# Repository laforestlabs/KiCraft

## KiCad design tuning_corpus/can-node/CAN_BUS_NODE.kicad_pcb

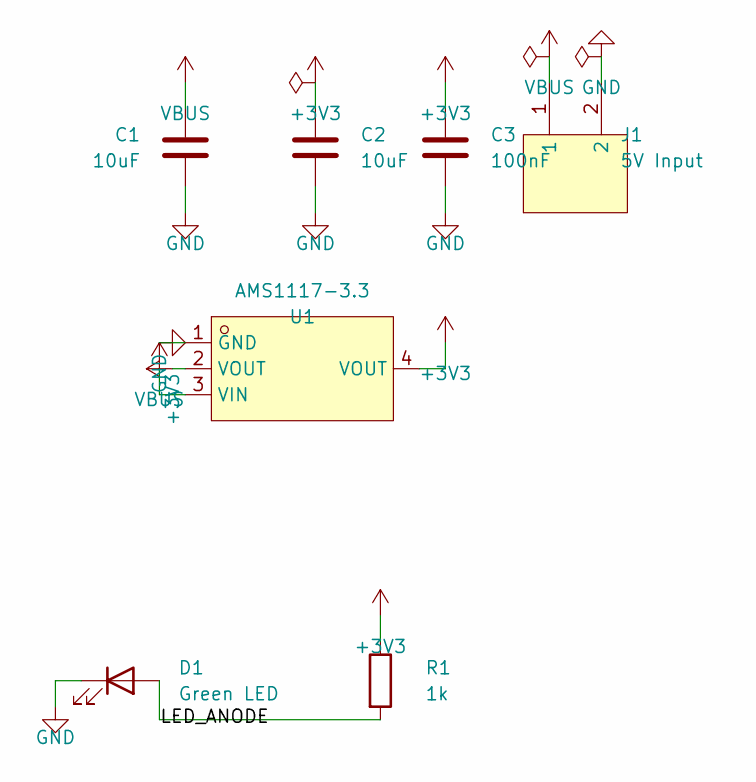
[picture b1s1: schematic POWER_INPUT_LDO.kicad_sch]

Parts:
C1, C2: 10uF; C_0805_2012Metric
C3: 100nF; C_0805_2012Metric
D1: Green LED; LED_0805_2012Metric
J1: 5V Input; CONN-TH_WJ126V-5.0-2P
R1: 1k; R_0805_2012Metric
U1: AMS1117-3.3; SOT-223-3_L6.5-W3.4-P2.30-LS7.0-BR

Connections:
LED_ANODE: D1.2 (A), R1.2

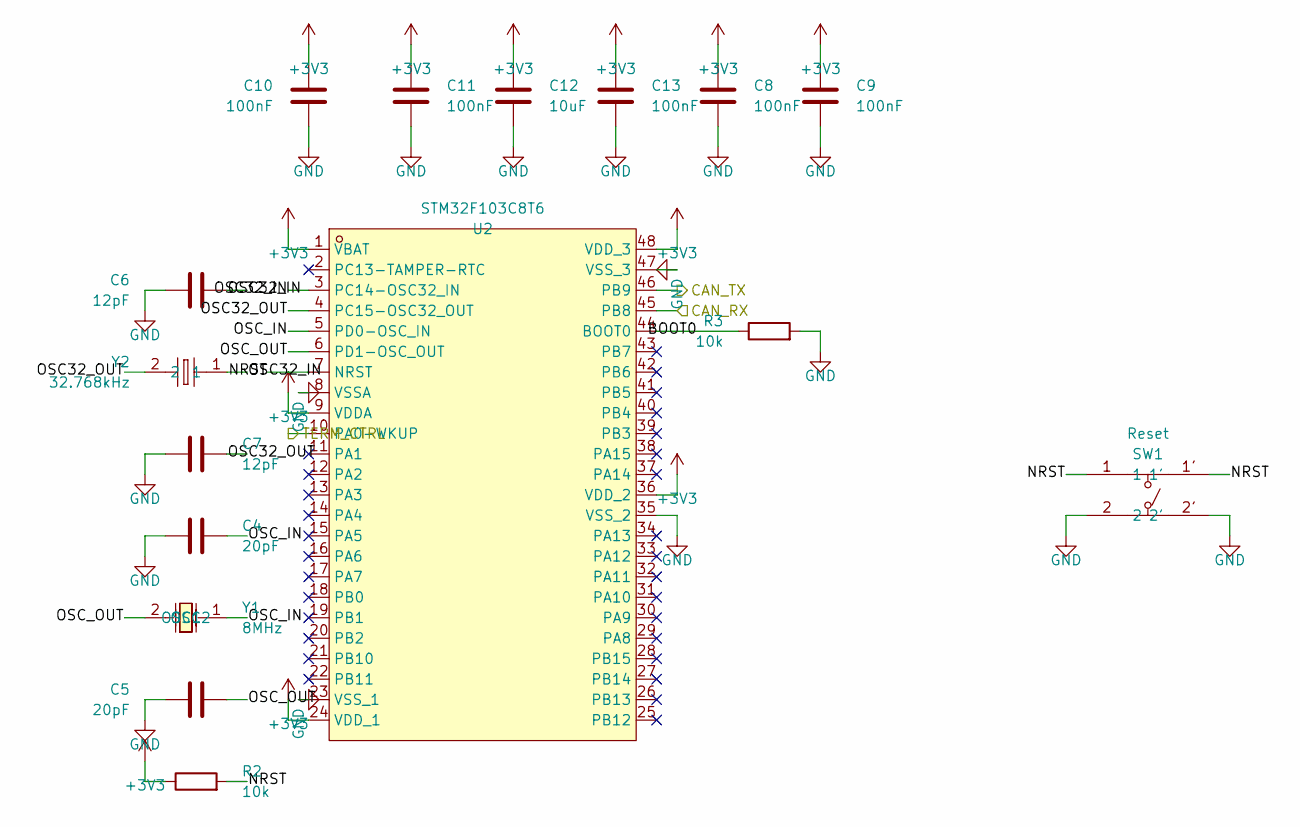
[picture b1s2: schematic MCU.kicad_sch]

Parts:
C4, C5: 20pF; C_0805_2012Metric
C6, C7: 12pF; C_0805_2012Metric
C8, C9, C10, C11, C13: 100nF; C_0805_2012Metric
C12: 10uF; C_0805_2012Metric
R2, R3: 10k; R_0805_2012Metric
SW1: Reset; SW-SMD_EVQP7A01P
U2: STM32F103C8T6; LQFP-48_L7.0-W7.0-P0.50-LS9.0-BL
Y1: 8MHz; CRYSTAL-SMD_L11.5-W4.8-LS12.7
Y2: 32.768kHz; OSC-SMD_L3.2-W1.5

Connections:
BOOT0: R3.1, U2.44 (BOOT0)
CAN_RX: U2.45 (PB8); also elsewhere on the board
CAN_TX: U2.46 (PB9); also elsewhere on the board
NRST: R2.2, SW1.1, SW1.1', U2.7 (NRST)
OSC32_IN: C6.1, U2.3 (PC14-OSC32_IN), Y2.1
OSC32_OUT: C7.1, U2.4 (PC15-OSC32_OUT), Y2.2
OSC_IN: C4.1, U2.5 (PD0-OSC_IN), Y1.1 (OSC1)
OSC_OUT: C5.1, U2.6 (PD1-OSC_OUT), Y1.2 (OSC2)
TERM_CTRL: U2.10 (PA0-WKUP); also elsewhere on the board

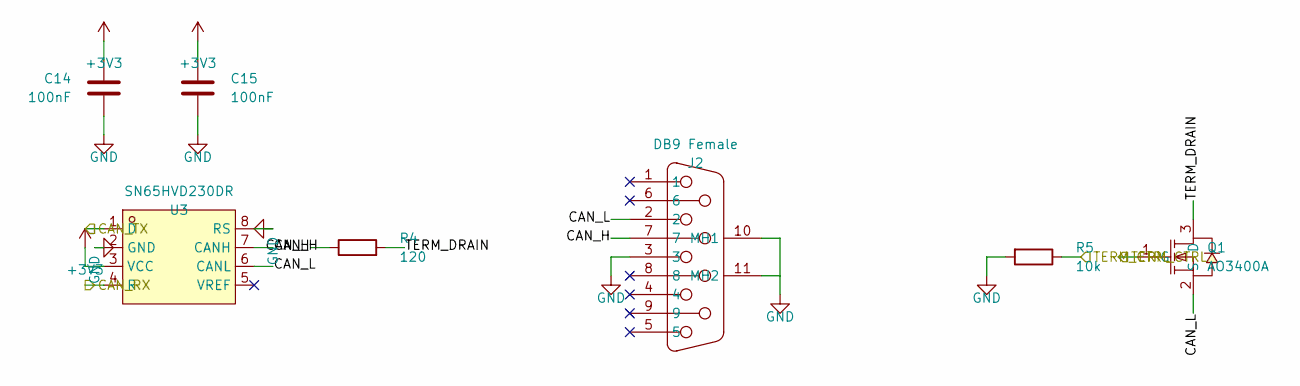
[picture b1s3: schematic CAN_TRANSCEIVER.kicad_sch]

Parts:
C14, C15: 100nF; C_0805_2012Metric
J2: DB9 Female; DSUB-TH_DMR-9S
Q1: AO3400A; SOT-23-3_L2.9-W1.3-P1.90-LS2.4-BR
R4: 120; R_0805_2012Metric
R5: 10k; R_0805_2012Metric
U3: SN65HVD230DR; SOIC-8_L4.9-W3.9-P1.27-LS6.0-BL

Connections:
CAN_H: J2.7, R4.1, U3.7 (CANH)
CAN_L: J2.2, Q1.2 (S), U3.6 (CANL)
CAN_RX: U3.4 (R); also elsewhere on the board
CAN_TX: U3.1 (D); also elsewhere on the board
TERM_CTRL: Q1.1 (G), R5.1; also elsewhere on the board
TERM_DRAIN: Q1.3 (D), R4.2

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
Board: 2 copper layers, 30 parts (0 on the bottom side), 16 nets, no tracks yet.

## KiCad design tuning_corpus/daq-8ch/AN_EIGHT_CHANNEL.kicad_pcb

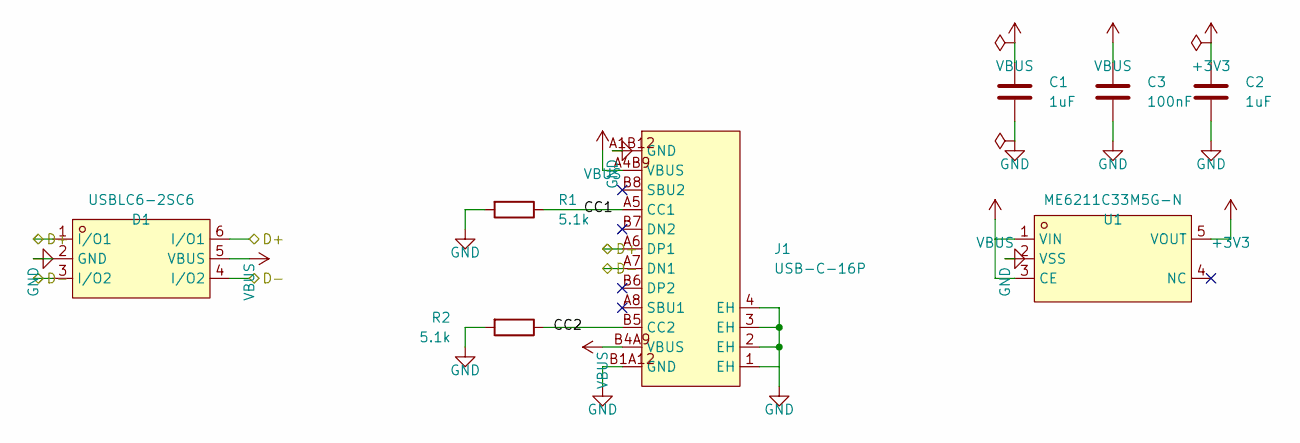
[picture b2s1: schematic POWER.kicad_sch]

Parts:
C1, C2: 1uF; C_0805_2012Metric
C3: 100nF; C_0805_2012Metric
D1: USBLC6-2SC6; SOT-23-6_L2.9-W1.6-P0.95-LS2.8-BL
J1: USB-C-16P; USB-C_SMD-TYPE-C-31-M-12_1
R1, R2: 5.1k; R_0805_2012Metric
U1: ME6211C33M5G-N; SOT-23-5_L3.0-W1.7-P0.95-LS2.8-BL

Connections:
CC1: J1.A5 (CC1), R1.1
CC2: J1.B5 (CC2), R2.1
D+: D1.1 (I/O1), D1.6 (I/O1), J1.A6 (DP1); also elsewhere on the board
D-: D1.3 (I/O2), D1.4 (I/O2), J1.A7 (DN1); also elsewhere on the board

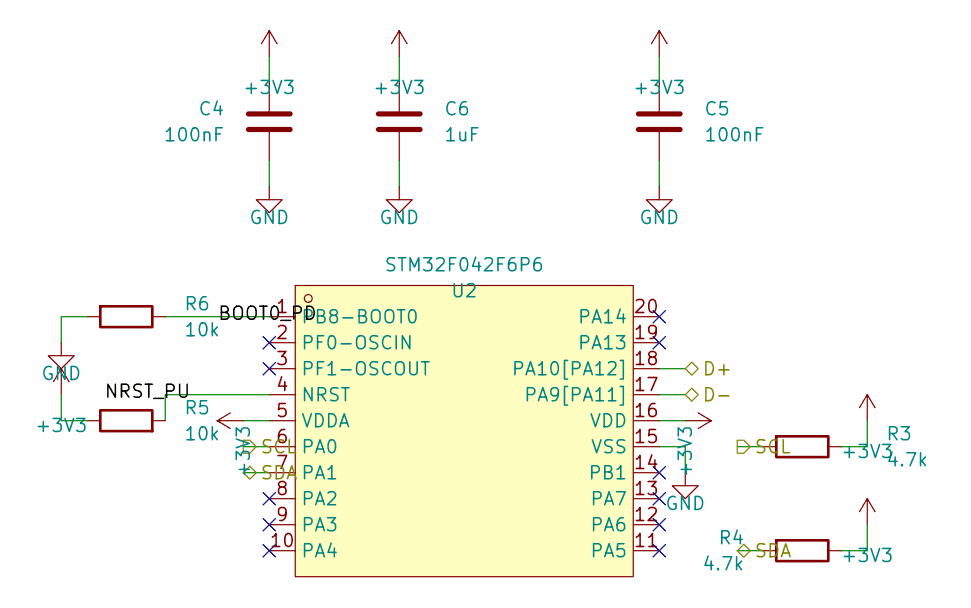
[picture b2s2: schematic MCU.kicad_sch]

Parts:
C4, C5: 100nF; C_0805_2012Metric
C6: 1uF; C_0805_2012Metric
R3, R4: 4.7k; R_0805_2012Metric
R5, R6: 10k; R_0805_2012Metric
U2: STM32F042F6P6; TSSOP-20_L6.5-W4.4-P0.65-LS6.4-BL

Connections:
BOOT0_PD: R6.1, U2.1 (PB8-BOOT0)
D+: U2.18 (PA10[PA12]); also elsewhere on the board
D-: U2.17 (PA9[PA11]); also elsewhere on the board
NRST_PU: R5.2, U2.4 (NRST)
SCL: R3.2, U2.6 (PA0); also elsewhere on the board
SDA: R4.2, U2.7 (PA1); also elsewhere on the board

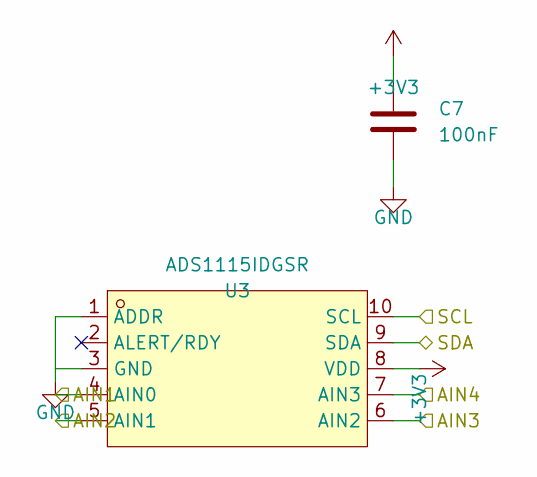
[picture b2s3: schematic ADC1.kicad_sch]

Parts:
C7: 100nF; C_0805_2012Metric
U3: ADS1115IDGSR; MSOP-10_L3.0-W3.0-P0.50-LS5.0-BL

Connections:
AIN1: U3.4 (AIN0); also elsewhere on the board
AIN2: U3.5 (AIN1); also elsewhere on the board
AIN3: U3.6 (AIN2); also elsewhere on the board
AIN4: U3.7 (AIN3); also elsewhere on the board
SCL: U3.10 (SCL); also elsewhere on the board
SDA: U3.9 (SDA); also elsewhere on the board

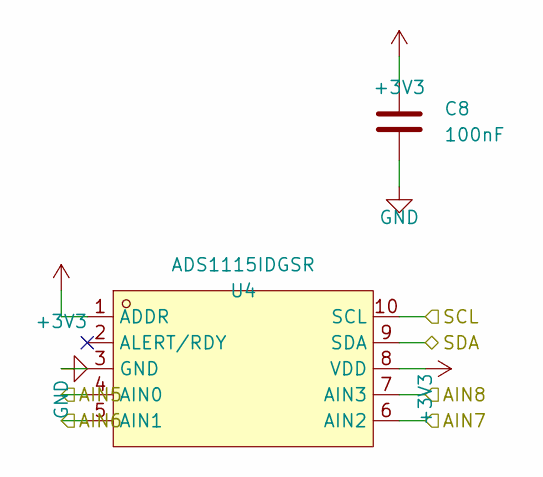
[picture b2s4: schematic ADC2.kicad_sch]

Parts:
C8: 100nF; C_0805_2012Metric
U4: ADS1115IDGSR; MSOP-10_L3.0-W3.0-P0.50-LS5.0-BL

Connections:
AIN5: U4.4 (AIN0); also elsewhere on the board
AIN6: U4.5 (AIN1); also elsewhere on the board
AIN7: U4.6 (AIN2); also elsewhere on the board
AIN8: U4.7 (AIN3); also elsewhere on the board
SCL: U4.10 (SCL); also elsewhere on the board
SDA: U4.9 (SDA); also elsewhere on the board

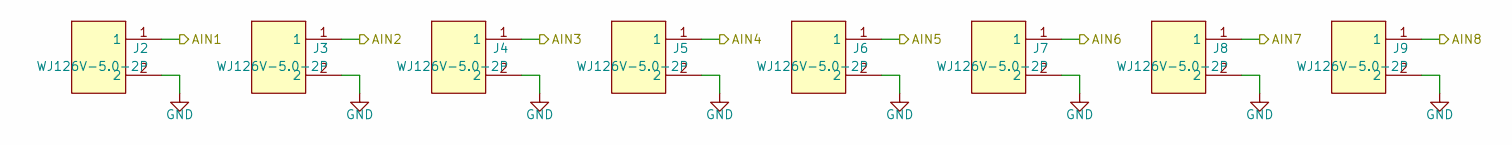
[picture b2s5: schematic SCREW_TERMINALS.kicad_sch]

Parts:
J2, J3, J4, J5, J6, J7, J8, J9: WJ126V-5.0-2P; CONN-TH_WJ126V-5.0-2P

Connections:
AIN1: J2.1; also elsewhere on the board
AIN2: J3.1; also elsewhere on the board
AIN3: J4.1; also elsewhere on the board
AIN4: J5.1; also elsewhere on the board
AIN5: J6.1; also elsewhere on the board
AIN6: J7.1; also elsewhere on the board
AIN7: J8.1; also elsewhere on the board
AIN8: J9.1; also elsewhere on the board

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
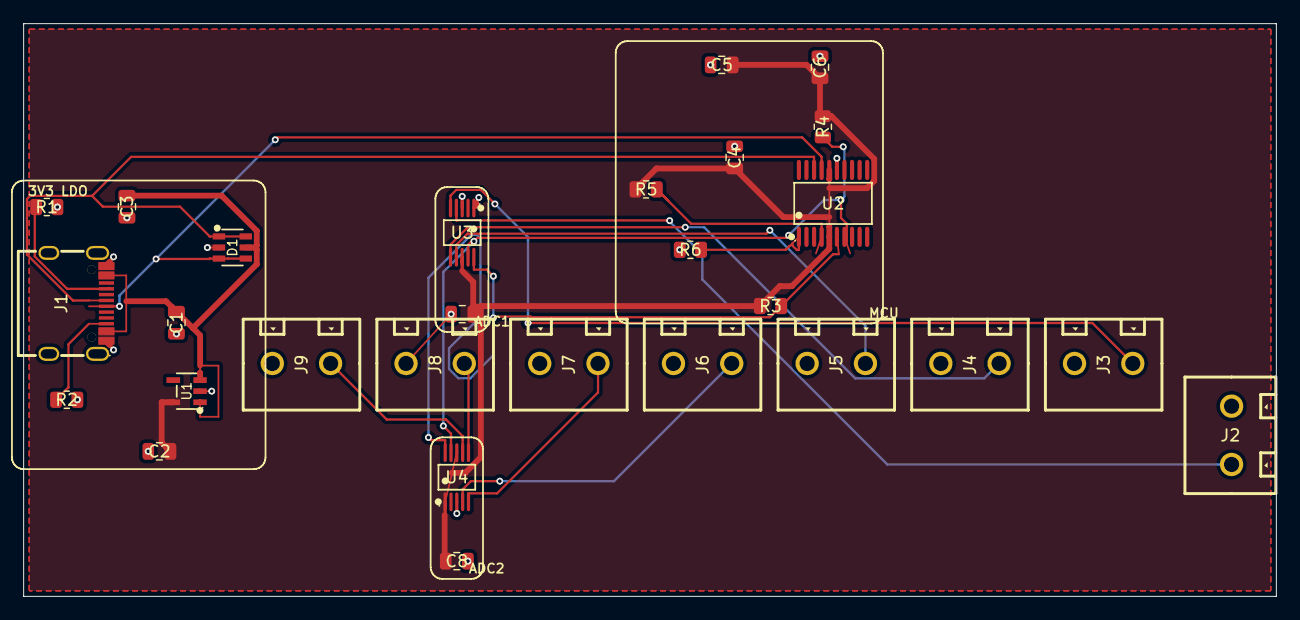
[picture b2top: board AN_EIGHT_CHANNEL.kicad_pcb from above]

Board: 2 copper layers, 107.5 x 49.1 mm, 28 parts (0 on the bottom side), 19 nets.

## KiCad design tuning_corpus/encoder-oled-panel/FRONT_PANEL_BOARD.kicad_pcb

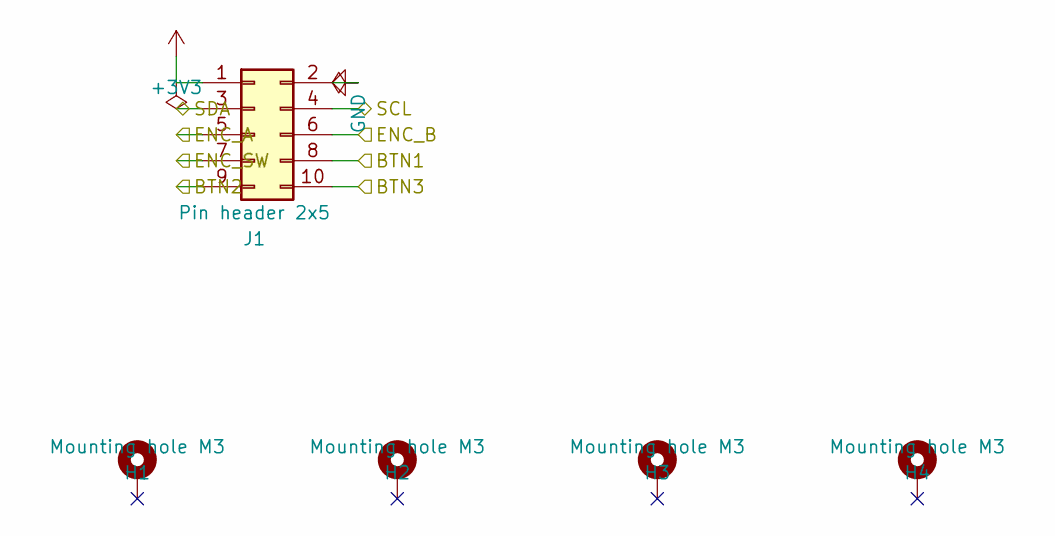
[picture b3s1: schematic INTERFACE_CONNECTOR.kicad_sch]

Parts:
H1, H2, H3, H4: Mounting hole M3; MountingHole_3.2mm_M3_Pad_TopBottom
J1: Pin header 2x5; PinHeader_2x05_P2.54mm_Vertical

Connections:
BTN1: J1.8; also elsewhere on the board
BTN2: J1.9; also elsewhere on the board
BTN3: J1.10; also elsewhere on the board
ENC_A: J1.5; also elsewhere on the board
ENC_B: J1.6; also elsewhere on the board
ENC_SW: J1.7; also elsewhere on the board
SCL: J1.4; also elsewhere on the board
SDA: J1.3; also elsewhere on the board

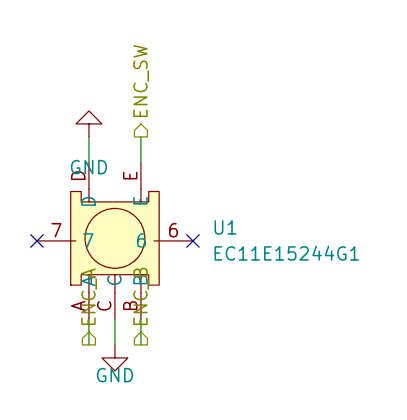
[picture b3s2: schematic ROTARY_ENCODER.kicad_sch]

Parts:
U1: EC11E15244G1; SW-TH_EC11E15244G1

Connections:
ENC_A: U1.A; also elsewhere on the board
ENC_B: U1.B; also elsewhere on the board
ENC_SW: U1.E; also elsewhere on the board

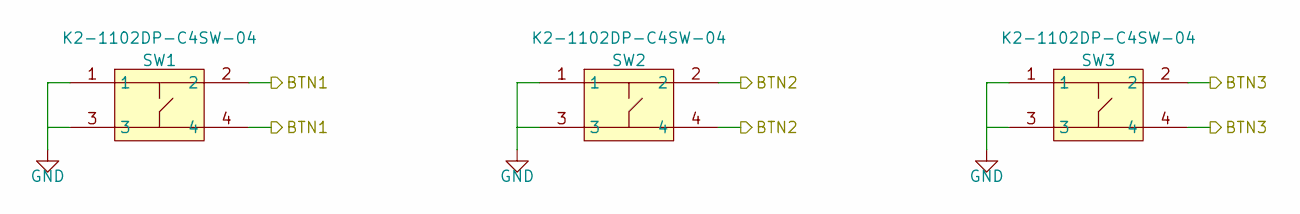
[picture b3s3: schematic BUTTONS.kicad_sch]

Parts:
SW1, SW2, SW3: K2-1102DP-C4SW-04; KEY-TH_4P-L6.0-W6.0-P4.50-LS6.50

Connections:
BTN1: SW1.2, SW1.4; also elsewhere on the board
BTN2: SW2.2, SW2.4; also elsewhere on the board
BTN3: SW3.2, SW3.4; also elsewhere on the board

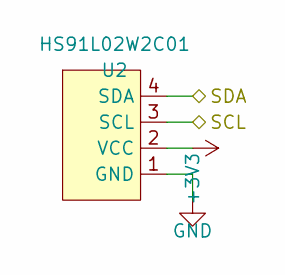
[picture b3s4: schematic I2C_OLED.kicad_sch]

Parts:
U2: HS91L02W2C01; OLED-TH_L38.0-W12.0_HS91L02W2C01

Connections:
SCL: U2.3 (SCL); also elsewhere on the board
SDA: U2.4 (SDA); also elsewhere on the board

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
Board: 2 copper layers, 10 parts (0 on the bottom side), 10 nets, no tracks yet.

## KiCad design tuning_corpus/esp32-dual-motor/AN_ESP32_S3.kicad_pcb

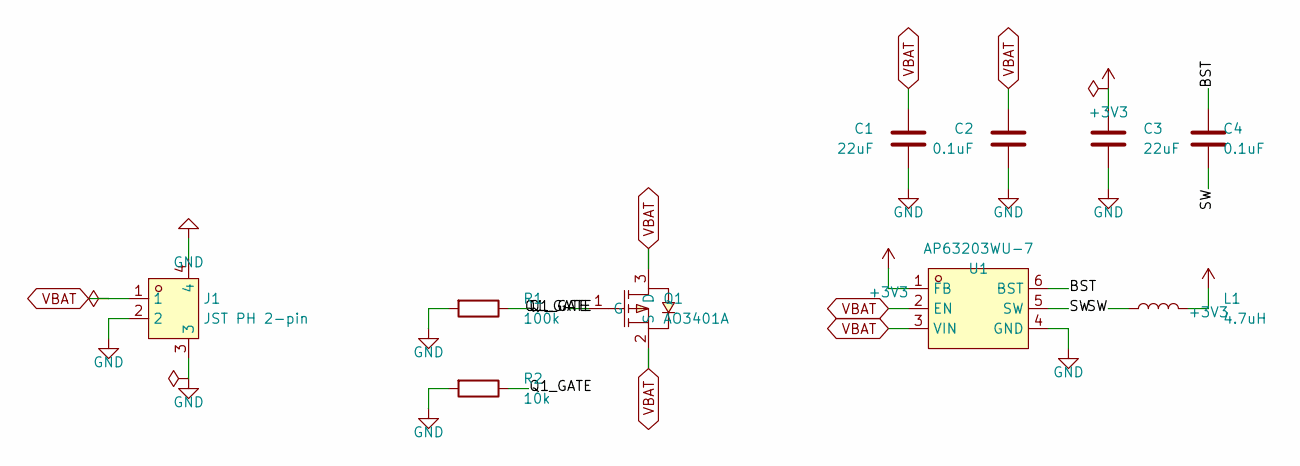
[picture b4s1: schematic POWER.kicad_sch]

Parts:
C1, C3: 22uF; C_0805_2012Metric
C2, C4: 0.1uF; C_0805_2012Metric
J1: JST PH 2-pin; CONN-SMD_P2.00_S2B-PH-SM4-TB-LF-SN
L1: 4.7uH; L_1206_3216Metric
Q1: AO3401A; SOT-23_L2.9-W1.3-P1.90-LS2.4-BR
R1: 100k; R_0805_2012Metric
R2: 10k; R_0805_2012Metric
U1: AP63203WU-7; TSOT-26_L2.9-W1.6-P0.95-LS2.8-BL

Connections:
BST: C4.1, U1.6 (BST)
Q1_GATE: Q1.1 (G), R1.1, R2.1
SW: C4.2, L1.1, U1.5 (SW)

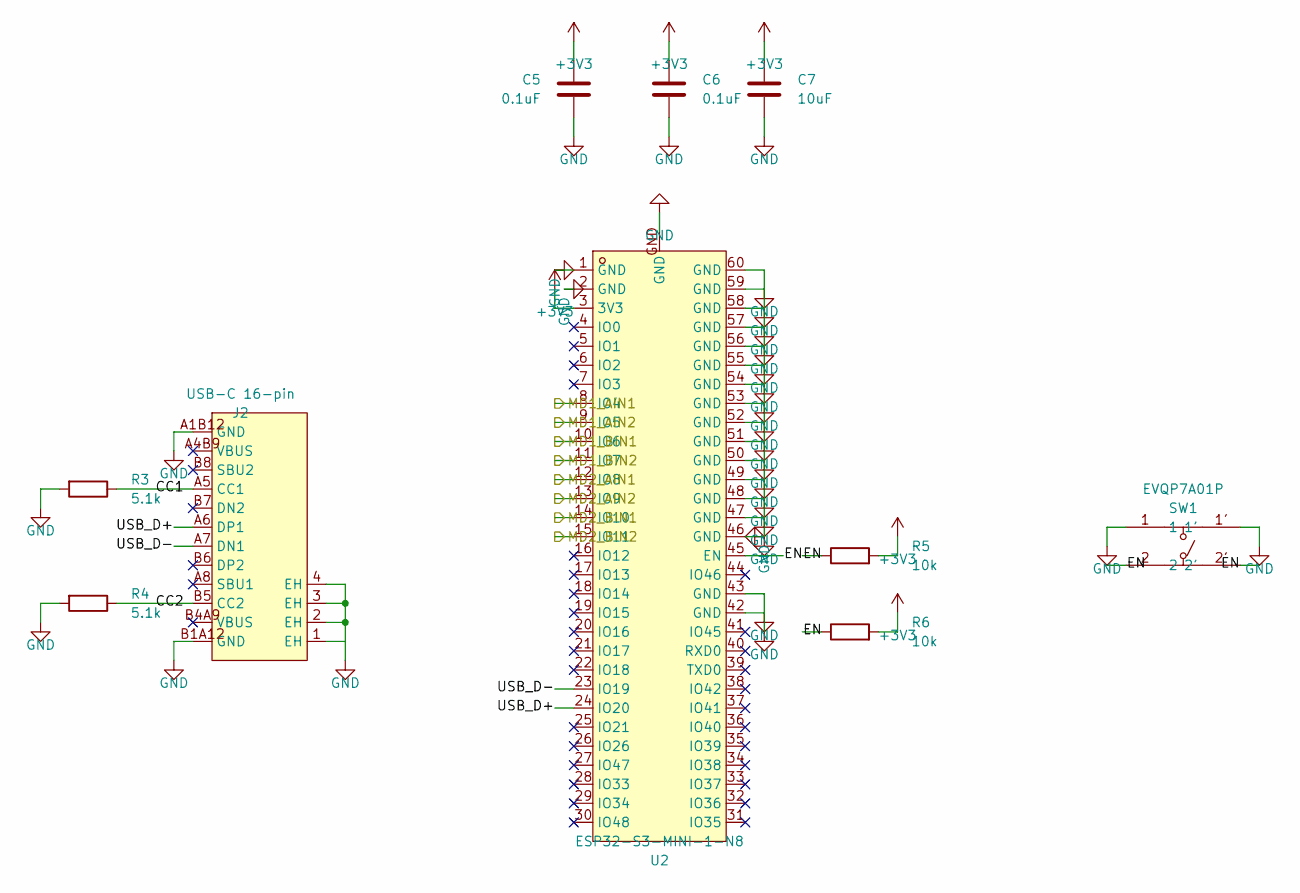
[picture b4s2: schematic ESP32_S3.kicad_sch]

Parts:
C5, C6: 0.1uF; C_0805_2012Metric
C7: 10uF; C_0805_2012Metric
J2: USB-C 16-pin; USB-C_SMD-TYPE-C-31-M-12_1
R3, R4: 5.1k; R_0805_2012Metric
R5, R6: 10k; R_0805_2012Metric
SW1: EVQP7A01P; SW-SMD_EVQP7A01P
U2: ESP32-S3-MINI-1-N8; BULETM-SMD_ESP32-S3-MINI-1-N8

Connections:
CC1: J2.A5 (CC1), R3.1
CC2: J2.B5 (CC2), R4.1
EN: R5.1, R6.1, SW1.2, SW1.2', U2.45 (EN)
MD1_AIN1: U2.8 (IO4); also elsewhere on the board
MD1_AIN2: U2.9 (IO5); also elsewhere on the board
MD1_BIN1: U2.10 (IO6); also elsewhere on the board
MD1_BIN2: U2.11 (IO7); also elsewhere on the board
MD2_AIN1: U2.12 (IO8); also elsewhere on the board
MD2_AIN2: U2.13 (IO9); also elsewhere on the board
MD2_BIN1: U2.14 (IO10); also elsewhere on the board
MD2_BIN2: U2.15 (IO11); also elsewhere on the board
USB_D+: J2.A6 (DP1), U2.24 (IO20)
USB_D-: J2.A7 (DN1), U2.23 (IO19)

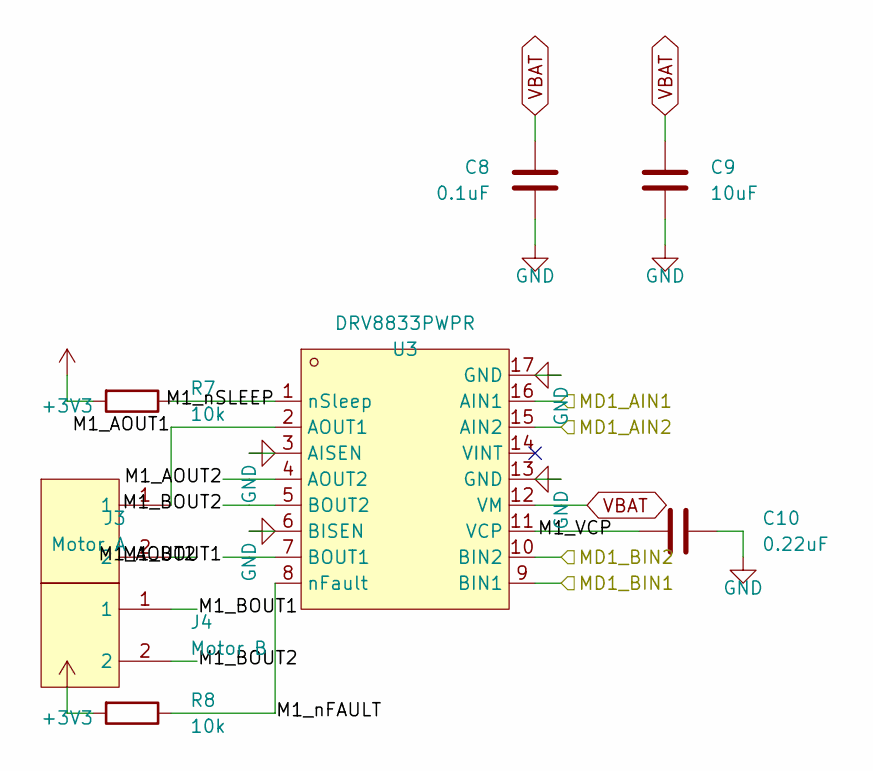
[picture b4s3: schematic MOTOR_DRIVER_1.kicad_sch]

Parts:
C8: 0.1uF; C_0805_2012Metric
C9: 10uF; C_0805_2012Metric
C10: 0.22uF; C_0805_2012Metric
J3: Motor A; CONN-TH_WJ126V-5.0-2P
J4: Motor B; CONN-TH_WJ126V-5.0-2P
R7, R8: 10k; R_0805_2012Metric
U3: DRV8833PWPR; TSSOP-16_L5.0-W4.4-P0.65-LS6.4-BL-EP

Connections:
M1_AOUT1: J3.1, U3.2 (AOUT1)
M1_AOUT2: J3.2, U3.4 (AOUT2)
M1_BOUT1: J4.1, U3.7 (BOUT1)
M1_BOUT2: J4.2, U3.5 (BOUT2)
M1_VCP: C10.1, U3.11 (VCP)
M1_nFAULT: R8.1, U3.8 (nFault)
M1_nSLEEP: R7.1, U3.1 (nSleep)
MD1_AIN1: U3.16 (AIN1); also elsewhere on the board
MD1_AIN2: U3.15 (AIN2); also elsewhere on the board
MD1_BIN1: U3.9 (BIN1); also elsewhere on the board
MD1_BIN2: U3.10 (BIN2); also elsewhere on the board

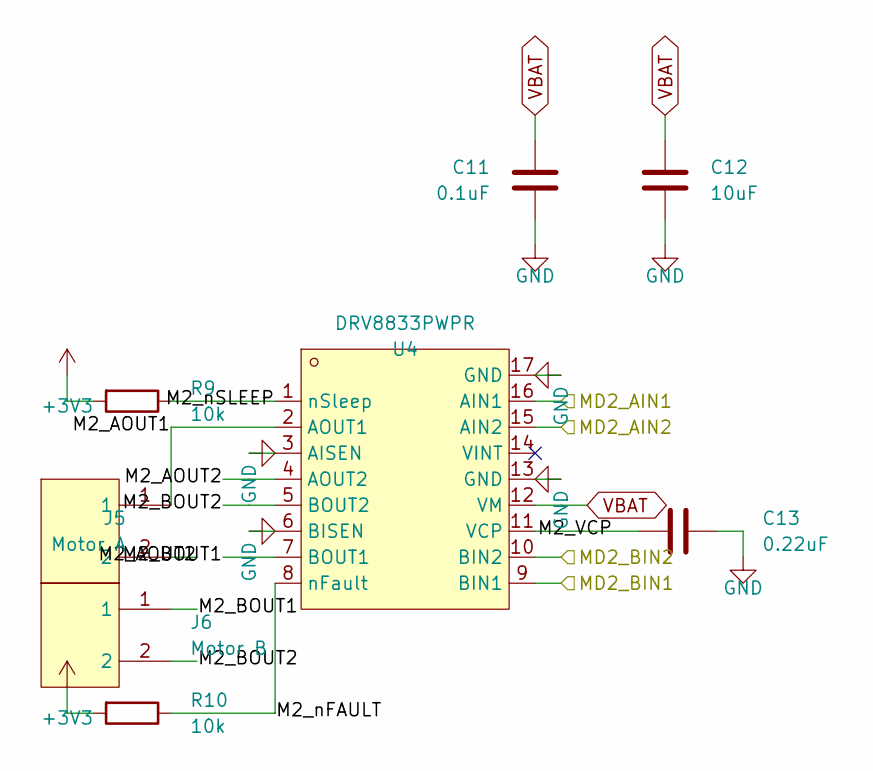
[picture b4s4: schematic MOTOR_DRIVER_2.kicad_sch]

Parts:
C11: 0.1uF; C_0805_2012Metric
C12: 10uF; C_0805_2012Metric
C13: 0.22uF; C_0805_2012Metric
J5: Motor A; CONN-TH_WJ126V-5.0-2P
J6: Motor B; CONN-TH_WJ126V-5.0-2P
R9, R10: 10k; R_0805_2012Metric
U4: DRV8833PWPR; TSSOP-16_L5.0-W4.4-P0.65-LS6.4-BL-EP

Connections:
M2_AOUT1: J5.1, U4.2 (AOUT1)
M2_AOUT2: J5.2, U4.4 (AOUT2)
M2_BOUT1: J6.1, U4.7 (BOUT1)
M2_BOUT2: J6.2, U4.5 (BOUT2)
M2_VCP: C13.1, U4.11 (VCP)
M2_nFAULT: R10.1, U4.8 (nFault)
M2_nSLEEP: R9.1, U4.1 (nSleep)
MD2_AIN1: U4.16 (AIN1); also elsewhere on the board
MD2_AIN2: U4.15 (AIN2); also elsewhere on the board
MD2_BIN1: U4.9 (BIN1); also elsewhere on the board
MD2_BIN2: U4.10 (BIN2); also elsewhere on the board

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
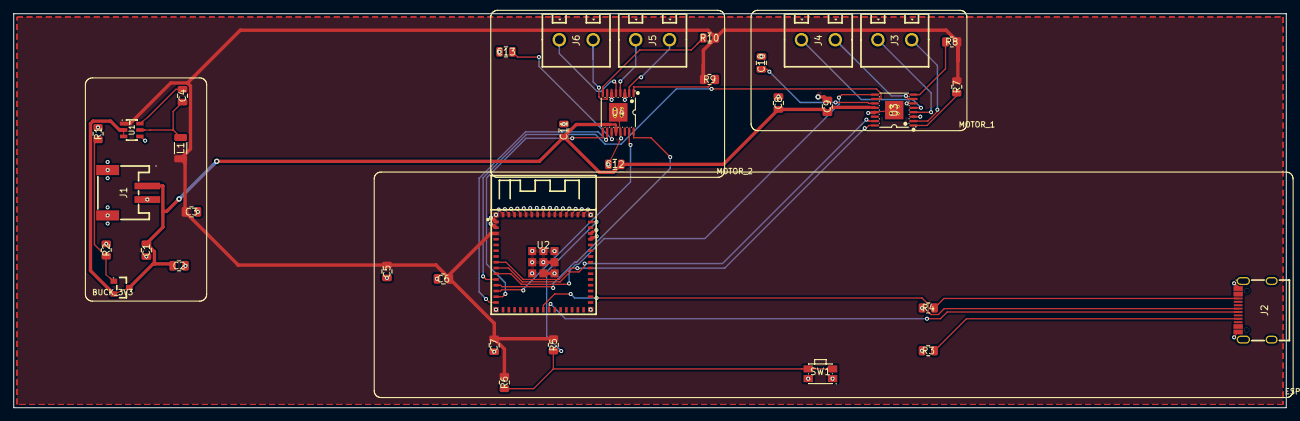
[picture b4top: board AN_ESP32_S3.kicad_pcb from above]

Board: 2 copper layers, 188.1 x 58.2 mm, 36 parts (0 on the bottom side), 33 nets.

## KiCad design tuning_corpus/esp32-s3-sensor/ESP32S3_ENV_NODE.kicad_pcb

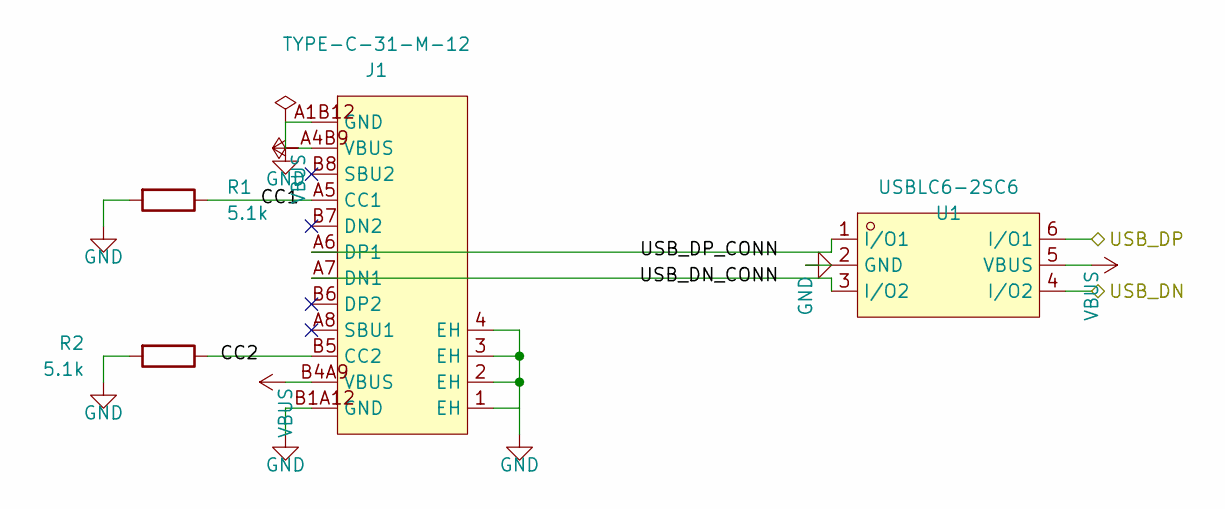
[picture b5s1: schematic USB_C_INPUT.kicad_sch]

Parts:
J1: TYPE-C-31-M-12; USB-C_SMD-TYPE-C-31-M-12_1
R1, R2: 5.1k; R_0805_2012Metric
U1: USBLC6-2SC6; SOT-23-6_L2.9-W1.6-P0.95-LS2.8-BL

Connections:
CC1: J1.A5 (CC1), R1.1
CC2: J1.B5 (CC2), R2.1
USB_DN: U1.4 (I/O2); also elsewhere on the board
USB_DN_CONN: J1.A7 (DN1), U1.3 (I/O2)
USB_DP: U1.6 (I/O1); also elsewhere on the board
USB_DP_CONN: J1.A6 (DP1), U1.1 (I/O1)

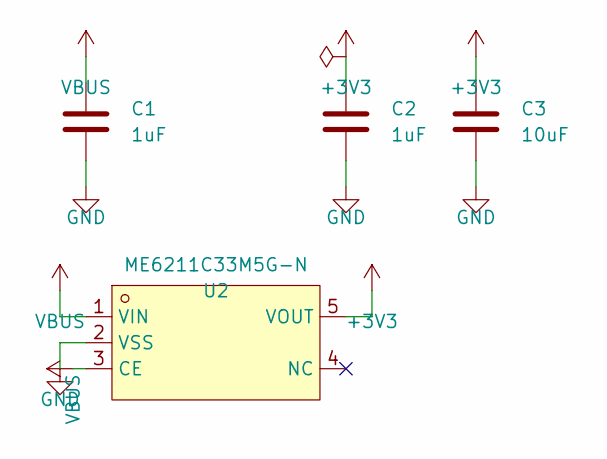
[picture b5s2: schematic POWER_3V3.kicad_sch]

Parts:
C1, C2: 1uF; C_0805_2012Metric
C3: 10uF; C_0805_2012Metric
U2: ME6211C33M5G-N; SOT-23-5_L3.0-W1.7-P0.95-LS2.8-BL

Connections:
+3V3: C2.1, C3.1, U2.5 (VOUT); also elsewhere on the board
